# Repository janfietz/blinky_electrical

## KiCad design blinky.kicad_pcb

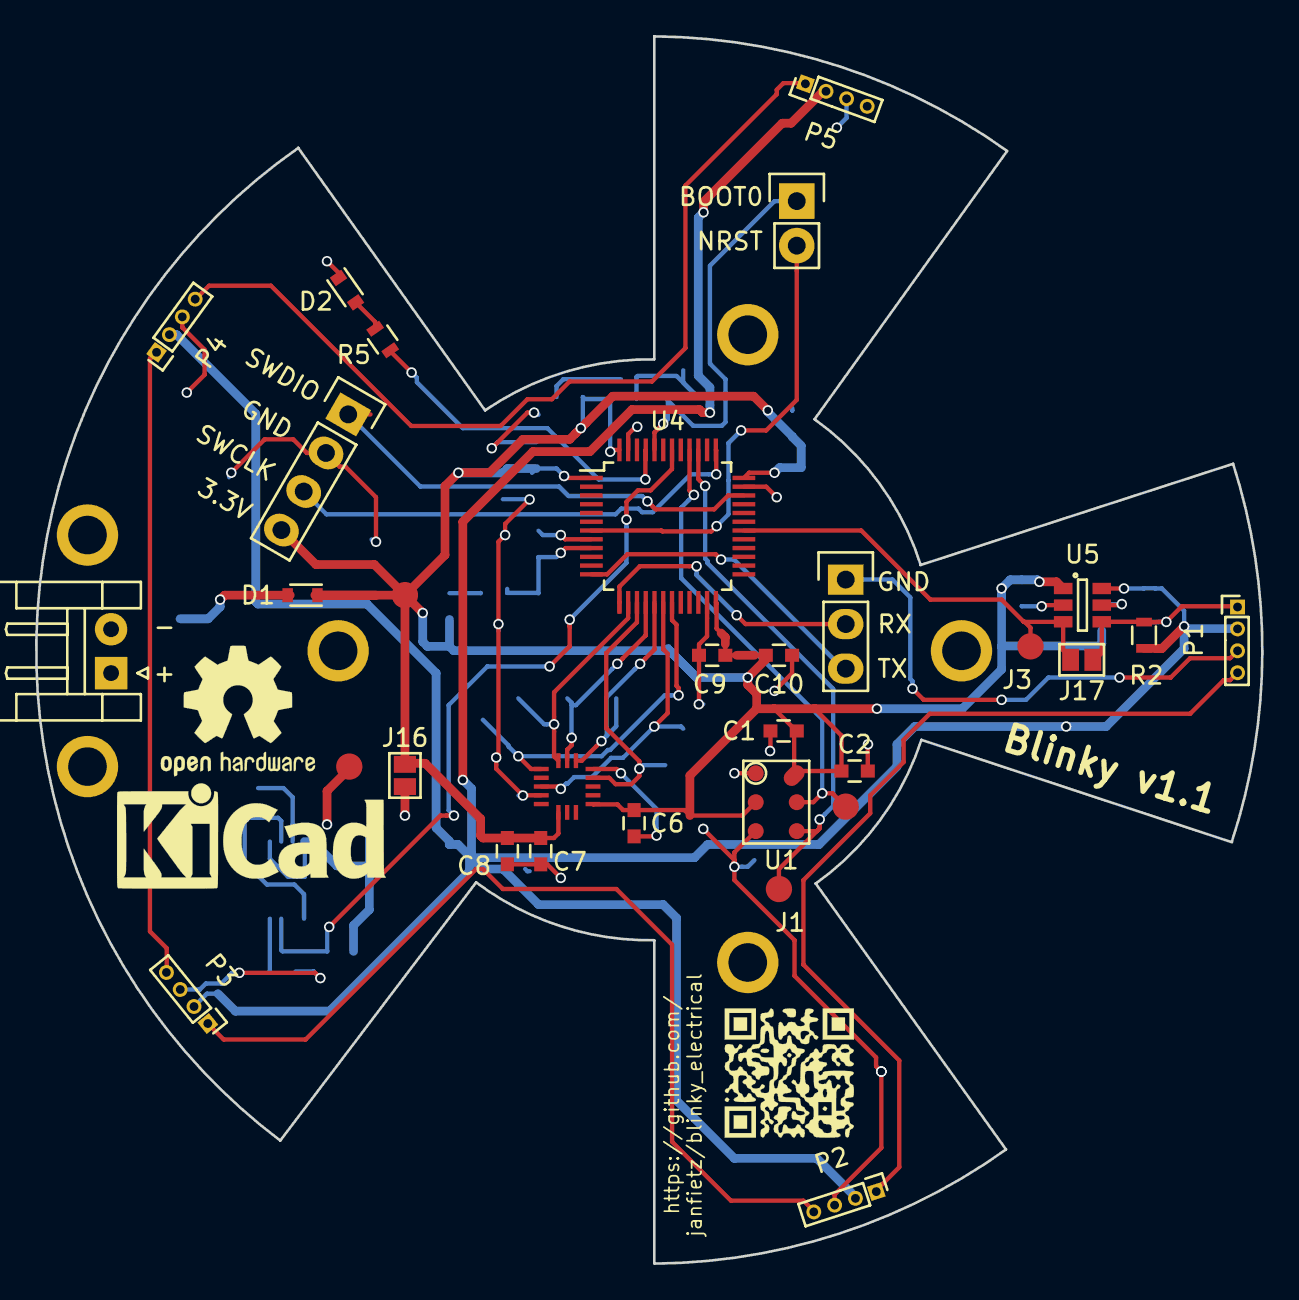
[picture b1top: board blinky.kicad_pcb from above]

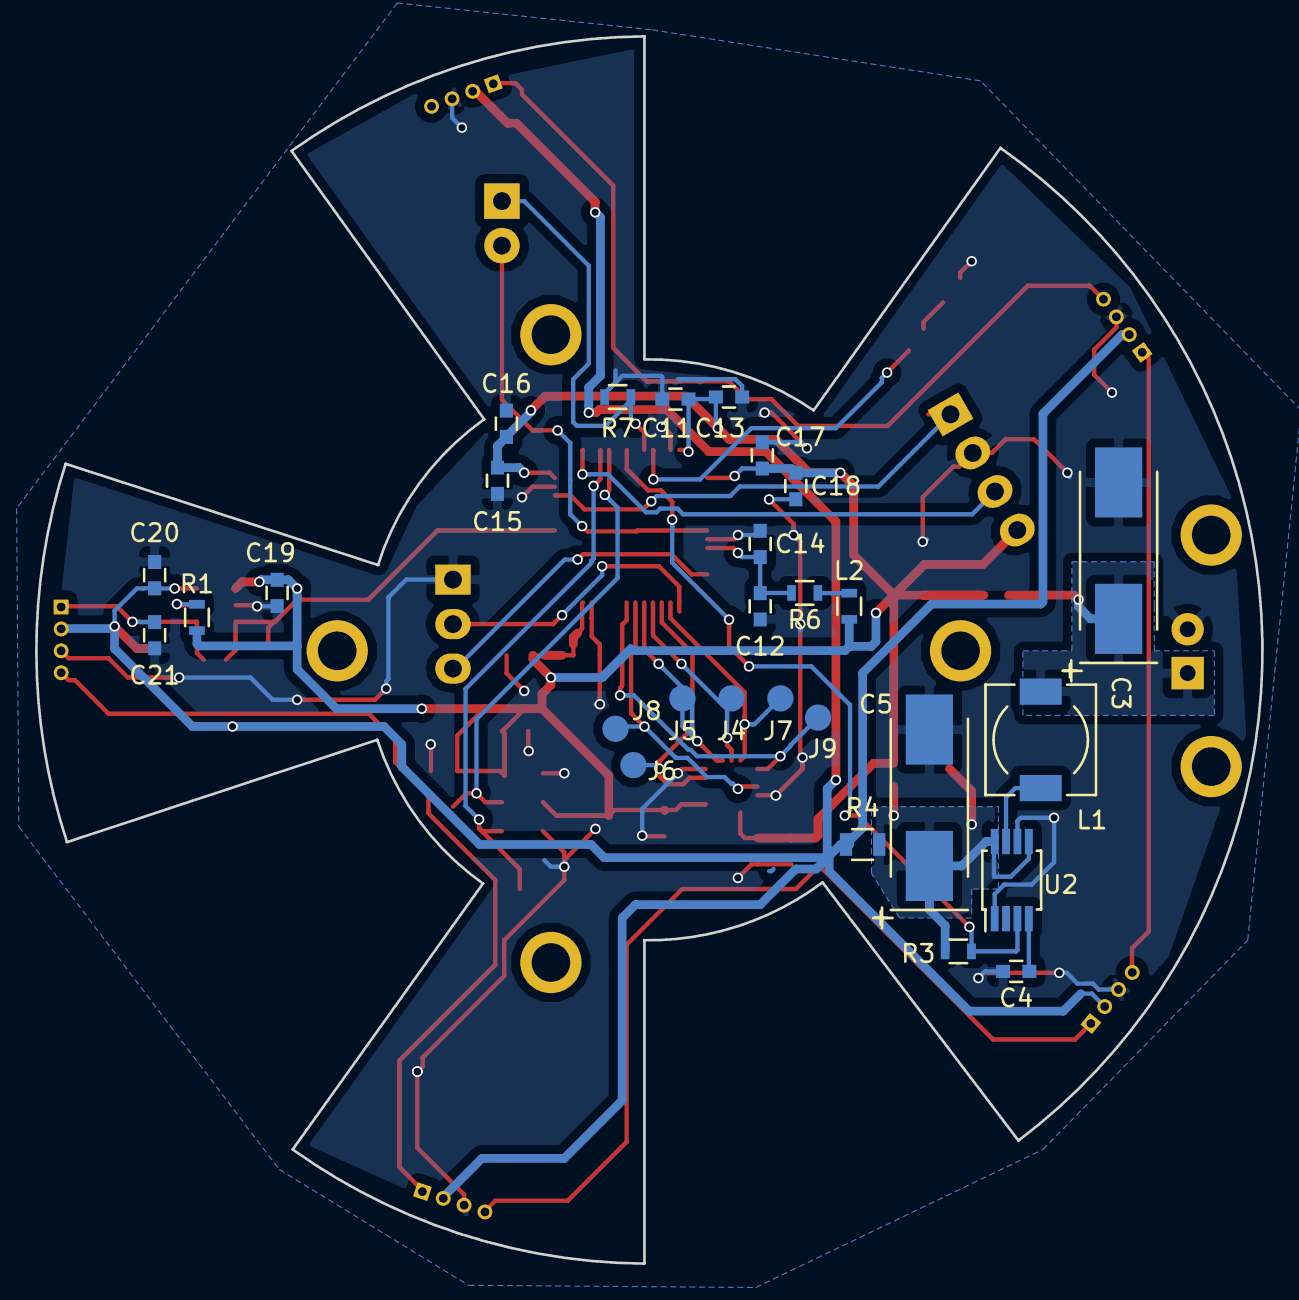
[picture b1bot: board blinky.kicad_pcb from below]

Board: 2 copper layers, 69.9 x 70.0 mm, 59 parts (28 on the bottom side), 33 nets.

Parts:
C1, C6, C8: 10uF; C_0603
C2, C4, C7, C9, C11, C12, C15, C17, C19: 100nF; C_0603
C3, C5: 47uF; TantalC_SizeD_EIA-7343_HandSoldering
C10, C13, C16, C18: Pol 4.7uF; C_0603
C14: 1uF; C_0603
C20, C21: NA; C_0603
D1: D_Schottky_0.1A_30V; D_0603
D2: LED; D_0603
J1: MIC_CLK; Measurement_Point_Round-SMD-Pad_Small
J2: MIC_DOUT; Measurement_Point_Round-SMD-Pad_Small
J3: LED_DIN; Measurement_Point_Round-SMD-Pad_Small
J4: ACCEL_MISO; Measurement_Point_Round-SMD-Pad_Small
J5: ACCEL_MOSI; Measurement_Point_Round-SMD-Pad_Small
J6: ACCEL_CLK; Measurement_Point_Round-SMD-Pad_Small
J7: ACCEL_CS; Measurement_Point_Round-SMD-Pad_Small
J8: ACCEL_INT1; Measurement_Point_Round-SMD-Pad_Small
J9: ACCEL_INT2; Measurement_Point_Round-SMD-Pad_Small
J10: DEBUG; Pin_Header_Straight_1x02
J11: SWD; Pin_Header_Straight_1x04
J12: BATTERY; JST_EH_S02B-EH_02x2.50mm_Angled
J13: UART; Pin_Header_Straight_1x03
J14: 5V; Measurement_Point_Round-SMD-Pad_Small
J15: 3V3; Measurement_Point_Round-SMD-Pad_Small
J16, J17: GS2
L1: 10uH; Choke_SMD_6.3x6.3_H3
L2: fcm1608; R_0603
P1, P2, P3, P4, P5: BUTTON; Pin_Header_Straight_1_04_Pitch1.25mm
R1, R2: NA; R_0603
R3: 100k; R_0603
R4: 0; R_0805
R5, R6: 0; R_0603
R7: 510; R_0603
U1: MP45DT02-M; HLGA-6L
U2: L6920DB; MSOP-8_3x3mm_Pitch0.65mm
U3: LIS3DH; LGA-16-3x3
U4: STM32F072X8; LQFP-48_7x7mm_Pitch0.5mm
U5: TXS0101; SOT-23-6

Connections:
+3V3: C1.1, C2.1, C6.1, C7.1, C8.1, C9.1, C10.1, C11.1, C13.1, C15.1, C16.1, C17.1, C18.1, C19.2, D1.1, J11.4, J15.1, J16.1, L2.1, R1.1, U1.2, U1.6, U3.1, U3.14, U4.1, U4.24, U4.36, U4.48, U5.1
+5V: C5.1, J14.1, J16.2, R3.1, R4.2, U2.5, U2.8
/ACCEL_CLK: J6.1, U3.4, U4.15
/ACCEL_CS: J7.1, U3.8, U4.14
/ACCEL_INT1: J8.1, U3.11, U4.18
/ACCEL_INT2: J9.1, U3.9, U4.19
/ACCEL_MISO: J4.1, U3.7, U4.16
/ACCEL_MOSI: J5.1, U3.6, U4.17
/BOOT0: J10.1, R7.1, U4.44
/LED5V_DATAIN: C21.1, J17.1, P1.1, R2.2, U5.4
/LED_5V: C20.2, P1.2, P2.2, P3.2, P4.2, P5.2, R2.1, R4.1, U5.6
/LED_DATAIN: J3.1, J17.2, U4.30, U5.3
/LED_HB: R5.1, U4.45
/MIC_CLK: J1.1, U1.4, U4.39
/MIC_DOUT: J2.1, U1.5, U4.40
/NRST: J10.2, U4.7
/POWER_LBO: R3.2, U2.3, U4.42
/SWCLK: J11.3, U4.37
/SWDIO: J11.1, U4.34
/UART2_RX: J13.2, U4.13
/UART2_TX: J13.3, U4.12
GND: C1.2, C2.2, C3.2, C4.2, C5.2, C6.2, C7.2, C8.2, C9.2, C10.2, C11.2, C12.2, C13.2, C14.2, C15.2, C16.2, C17.2, C18.2, C19.1, C20.1, C21.2, D2.1, J11.2, J12.2, J13.1, P1.3, P2.3, P3.3, P4.3, P5.3, R7.2, U1.1, U1.3, U2.1, U2.6, U3.5, U3.12, U4.8, U4.23, U4.35, U4.47, U5.2
unnamed: C4.1, U2.4
unnamed: D2.2, R5.2
unnamed: L1.2, U2.7
unnamed: L2.2, R6.2
unnamed: P1.4, P2.1
unnamed: P2.4, P3.1
unnamed: P3.4, P4.1
unnamed: P4.4, P5.1
unnamed: R1.2, U5.5
VDD: C3.1, D1.2, J12.1, L1.1
VDDA: C12.1, C14.1, R6.1, U4.9

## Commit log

2017-11-09 new voltage layout
2017-11-28 Add heartbeat led
2017-12-10 Add shortcut to enable 3V3 Only mode
2018-01-07 bump hash
2018-01-07 change level shifter
2018-01-07 uses 2mm pitch pin header for neopixel
2018-01-09 pcb: add qr code and axis
2018-01-12 submodules: bump hash
2018-02-28 new led pin footprints
